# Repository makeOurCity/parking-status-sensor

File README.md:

# 満空灯カラーセンサ読み取り PoC 設計書

> 駐車場の満空表示灯（満／空灯）の発光色をカラーセンサで外付け読み取りし、満車・空車状態をIoTデータとして取得する実証（PoC）の設計書。

- ステータス: PoC 実証フェーズ（LTE-M 版の試作機で試験中、LoRaWAN 版を実装中）
- 最終更新: 2026-09-29
- 管理: GitHub（本設計書・Issues・実装コードを同一リポジトリで管理）

---

## 1. 背景と目的

### 1.1 背景

駐車場の満空状態を取得する一般的な方法は、各車室へのセンサ設置や、入退場ゲートと連動した在車台数カウントである。これらは駐車場設備側ですでに処理されており、外部から新規に取得しようとすると設備への介入が必要になる。

一方、多くの駐車場では満空状態が「満／空」表示灯として可視化されている。本PoCは、この**既存の表示灯を外側から読み取る**ことで、設備に手を加えずに満空データを取得できないかを検証する。

### 1.2 目的（PoCのゴール）

- 満空表示灯の発光色を外付けカラーセンサで読み取り、「満／空」を判定できることを確認する。
- 設備（制御盤・配線）に一切介入しない、外付け・単機能・設置容易な構成で成立することを示す。
- 取得したデータを既存のデータ基盤（FIWARE Orion / NGSIv2）に連携できる見通しを得る。

### 1.3 PoCで「やらないこと」（スコープ外）

- 長期間の安定運用・耐久性の実証（PoC期間は数週間〜数ヶ月を想定。電池容量はそれ以上の余裕あり）。
- ソーラー等による自立電源での無人長期運用（将来オプションとして記載のみ）。
- 全表示方式への対応（後述のとおり「色切替型」に限定）。
- 製品化・量産設計・外部提供。

---

## 2. 対象の限定

### 2.1 満空表示灯の方式分類

調査の結果、世の中の満空表示灯は概ね以下の4タイプに分類される。

| タイプ | 説明 | 本PoCでの扱い |
|---|---|---|
| 色切替型 | 同一表示面で赤（満）↔緑（空）など色が変わる。LED式の主流。 | **対象（本命）** |
| フルドット型 | フルドットLEDで満/空/混/閉やアイコン・文字を表示。 | スコープ外（将来検討） |
| 回転式（メカ式） | 物理的に板が回転して満/空を切替。非発光。 | スコープ外（光で読めない） |
| 多階・複合表示型 | 立体駐車場で階別満空を1枚に集約表示。 | スコープ外（多点必要） |

### 2.2 本PoCの前提

- 対象は **色切替型（赤=満／緑=空 など、色で状態が変わるLED式）** に限定する。
- 表示方式を絞らないと実証設計が発散するため、まず最も普及している方式で成立性を確認する。
- 設置にあたり、表示灯設置者の貼り付け許可は得られている前提とする。

### 2.3 想定現場数

- PoC初期は **2〜3現場** を想定。
- 目的は「現場ごとの光条件下で赤緑判定が安定するか」のパターン収集。

---

## 3. 方式：センサ直貼り

### 3.1 採用方式

カメラで表示灯を撮影する方式ではなく、**表示灯の発光面にカラーセンサを直接貼り付け、その一点の色と明るさを読む**方式を採用する。

### 3.2 カメラ方式を採らない理由

| 課題 | カメラ方式 | センサ直貼り方式 |
|---|---|---|
| 設置位置 | 表示灯前方に設置場所と画角確保が必要 | 発光面に密着、位置問題なし |
| 外光・昼夜 | 露出・白飛び・反射の影響を受ける | 黒カッティングシート積層で外光を物理的に遮断 |
| 遮蔽 | 車両の通過で視界が遮られる | 密着のため遮蔽の影響なし |
| 処理負荷・電力 | 画像処理が必要で消費電力大 | 色の閾値比較のみ、超低消費 |

### 3.3 貼り付けの構造

センサ部は数mm角のチップだが、現場設置では **Grove - I2C Color Sensor V3.0** を含む小型パッチユニットを、**透明テープと黒カッティングシートの積層**で発光面に固定する。

**対象満空灯の構造（PoC 初回現場）**

- 表示面 **385×391 mm**、**透明アクリルカバー**、**額縁で縁を覆う**構造。
- 縁へのクリップ固定は不可。吸盤は落下リスクがあり採用しない。
- **透明テープで面全体を固定**し、落下リスクをゼロにする（安全上最重要）。
- **黒カッティングシート**が遮光層を兼ね、外光の混入を抑える。

```
      表示灯の発光面（透明アクリル）
  ┌─────────────────────────────┐
  │   満／空 の光                │
  └──────────────┬──────────────┘
                 │ 光
  ┌──────────────▼──────────────┐  ← 透明テープで全面固定
  │ 黒カッティングシート（遮光）  │
  │   ┌─────────────┐           │
  │   │ Grove Color │ ← 受光部  │
  │   │ Sensor V3.0 │           │
  │   └──────┬──────┘           │
  └──────────┼──────────────────┘
             │ Grove 4芯ケーブル
       ESP32本体（別筐体）へ
```

**受光位置**

- 画像分析の結果、LED 配列上では **下から2行目・左から2列目** 付近が推奨。
- 黒シートにセンサ受光窓を切り抜き、Grove Color Sensor V3.0 の受光部を窓に合わせる。

**運用上の留意**

- 発光面に乗るのはパッチのみ。ESP32 本体・電源は Grove ケーブルで分離し、表示灯裏や柱に固定する。
- 脱着はテープを剥がすだけ。仮設 PoC 用途に適合する。
- パッチは数 cm 角程度で、385 mm 面に対して面積比は小さく視認性への影響は限定的。

### 3.4 色切替型での判定ロジック

- カラーセンサが返す R・G・B 値を比較し、`R - G ≥ threshold なら満（赤）`、`G - R ≥ threshold なら空（緑）` と判定。
- R と G の差が一定閾値未満の場合は「不明」とし、消灯・遷移中の誤判定を回避する。
- 現場ごとの閾値はサーバ側パラメータとして保持し、端末/サーバ双方で判定可能にする。

---

## 4. システム構成

### 4.1 信号の流れ

```
[満空灯の発光面] 赤=満 / 緑=空
      │ 光
      ▼
[センサパッチ]  Grove Color Sensor V3.0 + 黒シート積層固定
      │ Grove I2C ケーブル
      ▼
[XIAO ESP32S3 + Grove Shield]  赤か緑か判定・送信   ← 電源: LiPo 電池（§6）
      │ LTE-M / Wi-Fi: MQTT over TLS      LoRaWAN: AWS IoT Core for LoRaWAN（#40）
      ▼
[AWS IoT Core]  受け口（ルールでトリガー）
      │
      ▼
[AWS Lambda]  ブリッジ（ペイロード変換 → NGSIv2 upsert）  ※現在はスタブ（受信ログを CloudWatch Logs に記録するだけ）。本実装は #7
      │
      ▼
[FIWARE Orion]  満空を登録
      │
      ▼
[STH-Comet]  履歴蓄積・読み取り精度の検証
```

端末は Orion に直接書き込まない。MQTT ペイロードの変換と NGSIv2 への upsert は Lambda（ブリッジ）が担う。

### 4.2 判定の持たせ方（端末／サーバ両対応）

- 端末は「生のセンサ値（RGB＋輝度）」と「端末内の暫定判定結果」の両方を送信する。
- サーバ側は生値で再判定も、端末判定の採用も選べる。
- 現場別閾値テーブルをサーバに持ち、必要なら端末にも配信。判定ロジックを端末/サーバどちらに寄せるかを後から変更可能にする。

### 4.3 通信方式

通信モジュールごとに版を分ける。**ビルド環境（PlatformIO env）で版を選び、モジュールの自動判別や共存はしない**（Grove UART ポートを LTE-M と LoRaWAN で排他利用するため）。

| 版 | モジュール | 状況 | 使い分け |
|---|---|---|---|
| **LoRaWAN 版** | Grove Wio-E5（STM32WLE5JC、技適付き） | 実装中（#40） | **本流**。現場にゲートウェイを置ける場合。送信が短く電池に有利 |
| **LTE-M 版** | M5Stack SIM7080G CAT-M Unit（M5STACK-U128）+ SORACOM SIM（plan-D / plan-KM1） | 実装済み・現地試験済み | LoRaWAN でどうしても通信できない場合 |
| Wi-Fi | ESP32-S3 内蔵 | ファーム対応済み | Wi-Fi を使える環境 |

- LTE-M 版は、送信するときだけ**ロードスイッチ基板**で LTE-M の電源を入れる（#88、基板評価中）。モデム内蔵の TLS で AWS IoT Core に直接つなぐ。旧方式のラッチングリレー（#46）は廃止した（経緯: [docs/25-low-power-phase2-hardware-cutoff.md](docs/25-low-power-phase2-hardware-cutoff.md) §2）。
- 送信データは判定結果＋生値のみで極小（数百バイト程度）。LoRaWAN の典型的なペイロードにも収まる。
- ファームの env と設定は [firmware/README.md](firmware/README.md) を参照。

### 4.4 FIWARE連携

- 満空フラグをNGSIv2でOrionにupsert。
- PoC段階では標準データモデルにこだわらず、独自エンティティ（例: `ParkingStatusSensor`）に `status`（満/空/不明）・生センサ値・タイムスタンプを載せる。
- STH-Cometで履歴化し読み取り精度を検証。方式確定後に `OffStreetParking` 等の標準属性へマッピングし直す。
- 投入は既存の moc-skill / GeonicDB CLI で運用可能。

---

## 5. 部品リスト（BOM）

### 5.1 確定BOM（試作1台分）

| 部品 | 型番 | 入手先 | 価格 | 備考 |
|---|---|---|---|---|
| マイコン | Seeed XIAO ESP32S3（無印） | 秋月電子 | ¥1,480 | 技適取得済(217-230892)。BAT はパッドのみ（JST 非搭載） |
| Grove Shield | Grove Shield for XIAO（103020312） | Seeed JP 等 | 約¥700 | 8×Grove（I2C×2・UART×1）。BAT パッド・充電管理付き |
| カラーセンサ | Grove - I2C Color Sensor V3.0（101021133） | Seeed Studio 等 | 約¥600 | VEML6040 搭載。I2C `0x10`。Grove コネクタ内蔵 |
| センサ接続 | Grove 4芯ケーブル 50〜100cm | Seeed / Amazon 等 | 約¥200〜400 | 標準配線（ピン入替不要。[wiring.md](docs/wiring.md)） |
| 閾値調整用ポテンショメーター | Grove - Rotary Angle Sensor | Seeed 等 | — | 現地での判定閾値の調整用（#60）。調整後は外してよい |
| バッテリー | LiPo 3.7V 4,400mAh 保護回路内蔵 JST-PH | ストロベリーリナックス | ¥550 | Grove Shield の BAT パッドへ JST で接続 |
| 配線・防水箱・固定材 | Grove ケーブル、IP65 樹脂箱、透明テープ・黒カッティングシート等 | Seeed / ホームセンター | 約¥2,000〜3,000 | 詳細は [docs/hardware.md](docs/hardware.md) 参照 |

**通信モジュール（版ごとにどちらか）**

| 部品 | 型番 | 入手先 | 価格 | 備考 |
|---|---|---|---|---|
| LoRaWAN モジュール | Grove - Wio-E5 | Seeed 等 | — | LoRaWAN 版。Grove UART 接続。常時通電 |
| LTE-M モジュール | M5Stack SIM7080G CAT-M Unit（M5STACK-U128） | スイッチサイエンス | ¥6,908 | LTE-M 版。Grove UART 接続 |
| SIM | SORACOM IoT SIM plan-D / plan-KM1 | SORACOMストア | ¥990（初期）+ ¥192/月〜 | LTE-M 版。ドコモ / KDDI 回線 |
| LTE-M 電源スイッチ基板 | 自作小基板 rev A（TI TPS22918、[hardware/lte-power-switch/](hardware/lte-power-switch/)） | JLCPCB（基板 + 実装） | $20.14（5 枚、送料込み） | LTE-M 版。LTE-M の電源を送信時だけ入れる（#88）。**rev A は Grove コネクタのピン番号が鏡像で、普通のケーブルでは使えない。rev B（2026-10-12 発注、$30.61）で直した** |

- 詳細な選定経緯・調達先 URL は [docs/hardware.md](docs/hardware.md)・[docs/bom.md](docs/bom.md) を参照。

### 5.2 部品選定の要点

- **マイコン**: カメラ不要なため無印 XIAO ESP32S3 で十分（Sense 版は不要）。LiPo 充電管理は Grove Shield 側にある。
- **センサ**: **Grove - I2C Color Sensor V3.0**（VEML6040 搭載）。
- **接続方式**: センサ・通信モジュール・LTE-M 電源スイッチ基板はすべて **Grove で接続**する（ピン入替・はんだ付け不要）。汎用性と組み立ての容易さを両立させ、LoRaWAN 版と LTE-M 版で構成を揃える。
- **バッテリー**: LiPo 電池を **Grove Shield の BAT パッド**に JST で接続（XIAO 本体には JST コネクタ非搭載）。モバイルバッテリーはオートパワーオフおよびパススルー時の瞬断が問題になるため不採用。

---

## 6. 電源方針

### 6.1 電源構成

- **LiPo 電池（3.7V 4,400mAh、保護回路内蔵）**を Grove Shield for XIAO の **BAT パッド**に JST で接続して運用する（はんだ付け前にテスターで極性を確認）。電源を引ける現場では USB 給電でも可。
- 電池で動かしているとき、**ESP32-S3 と Grove の各ポート（センサー・LTE-M を含む）は、Shield 上の降圧コンバーター（ETA3410）の 3.3V を共有する**。5V 系統は無効で、昇圧回路は使わない（[docs/hardware.md](docs/hardware.md)）。
- LTE-M モジュールは、送信するときだけロードスイッチ基板で通電する（#88、基板評価中）。
- 起床間隔は 5 分（`PSS_SLEEP_SECONDS=300`）。LTE-M 版は**状態が変わったときだけ送信**し、変わらなければ約 66 分に 1 回だけ定期送信する（`PSS_CHANGE_ONLY_SEND=1`、`PSS_HEARTBEAT_CYCLES=12`）。満空情報に秒単位の即時性は不要なので、この遅延は許容できる。

### 6.2 消費電力と稼働日数（LTE-M 版）

実測値（2026-09-29、`xiao-s3-aws-lte-relay-pot`、U200-1A 高速ロガーで約 44.5h 記録。詳細: [docs/74-brownout-conclusions.md](docs/74-brownout-conclusions.md) §4）:

| 項目 | 実測値 |
|---|---|
| Deep Sleep 中の電流 | 0.43 mA |
| 送信する起床 1 回（起床〜LTE 接続〜MQTT 送信〜切断〜Deep Sleep） | 16.8 秒・0.446 mAh |
| 送信しない起床 1 回（センサー読み取りのみ） | 4.8 秒・0.0475 mAh |

稼働日数の目安（LiPo 実効 3,960 mAh = 4,400 mAh × 90%）:

| シナリオ | 稼働日数 |
|---|---|
| 状態変化なし（約 66 分に 1 回の定期送信のみ） | **約 122 日** |
| 状態変化 1 日 20 回 | 約 98 日 |
| 毎回送信（worst case） | 約 29 日 |

**電池残量と充電の目安:** LTE-M 版は、電池の電圧が下がると LTE の送信時にブラウンアウトリセットが起き始める。1 回だけなら実害はほぼないが、そのまま放置すると送信できなくなる。**1 回目のブラウンアウト（テレメトリの `resetReason=brownout`）を「すぐ充電」の合図として扱う**。実際に使える日数は、上の表より短くなる（[docs/74-brownout-conclusions.md](docs/74-brownout-conclusions.md) §3.1）。

**LoRaWAN 版:** 送信が短く、TLS も不要なので、LTE-M 版より消費は小さい見込み（未実測、#40）。ゲートウェイを置ける現場では LoRaWAN を優先する（§4.3）。

### 6.3 ソーラー併用（将来オプション・PoCでは不採用）

将来の長期自立運用フェーズでのオプションとして記載のみ。初期PoCでは以下の理由で**不採用**とする。

- ソーラーパネルが現時点で比較的高価。
- 駐車場の設置状況により十分な日照が得られるか不明で、現地確認が前提。
- PoC段階では長期安定運用が要件外。

採用する場合の候補・留意点:
- 候補: MOTTERU MOT-SOLAR24（最大24W, USB-A, IP65）、Anker Solix PS30（27W, IP65）等。
- IP65防水はパネル部のみの製品が多く、パネルのみ屋外・バッテリ/ESP32は防水箱に収納。
- ソーラー併用時はバッテリーの「パススルー充電対応」「充放電切替時の出力瞬断なし」「低負荷時も高効率な充電制御IC(MPPT等)」を満たす機種を現物確認。

---

## 7. 関連事例・新規性

### 7.1 同種事例の調査結果

| 区分 | 状況 |
|---|---|
| 満空灯を後付け読み取りする事業・製品 | 見当たらない（応用先として空いている） |
| ほぼ同じ個人試作 | 1件あり。機器の電源ランプの色をカラーセンサ(S11059)＋ESP32で読む試作。「消灯=黒」の判定に課題。本設計の「差が小さければ不明」処理の妥当性を裏付け |
| 上位概念（表示灯の後付けIoT化） | 確立済み。PATLITE WDシステム（信号灯の後付けIoT化）等の製品、複数の特許が存在。技術的成立性は実証済み |

### 7.2 新規性の位置づけ

- 「光センサで人間用表示灯を外側から読みIoT化する」技術自体は枯れており、成立性は担保されている。
- 「**駐車場満空灯 × 自治体オープンデータ／FIWARE連携**」という応用は明確な先行事例が見当たらず、応用先として空いている。
- PoCで確かめるべきは技術成立性ではなく「現場光条件での赤緑安定判定」に集約される。

---

## 8. リスクと検証項目

### 8.1 PoCで潰す検証項目（優先順）

1. **生値の分離**: Grove Color Sensor V3.0（VEML6040）の R/G/B/W 生値が、満（赤）と空（緑）で十分なマージンを持って分離するか。透明カバー越し・拡散材ありの実機で確認。
2. **2状態以外の表示**: 消灯・点滅・整備中・深夜消灯等が現場にあるか棚卸しし、判定テーブルに「不明」状態を持たせる。
3. **電源運用**: 電池の電圧が下がったときにブラウンアウトが起き始める残量の確認（LTE-M 版、[docs/74-brownout-conclusions.md](docs/74-brownout-conclusions.md) §2.4）。LoRaWAN 版の消費電力の実測（#40）。

### 8.2 特許リスク

調査した米国特許 US11962293B2「Passive optical sensors」の権利範囲を確認した結果:

- この特許の新規部分は「**受動回路（FET＋蓄電）で、リレー接点ON/OFFのようなバイナリ出力を無電源で作る**」という回路構成にある。「ランプを光で読む」という目的自体は権利化されていない。
- 本PoC方式は「**能動的なマイコン(ESP32)＋デジタルI2Cカラーセンサ＋ソフトウェア判定**」であり、構成・動作原理が別物。抵触する見込みは低い。
- むしろ本方式は、当該特許が「従来技術（課題あり）」と位置づけるデジタルセンサ側であり、特許の新規部分の外側にある。
- ESP32＋カラーセンサでランプ色を読む構成は公知（個人事例あり）。

リスク評価:
- **PoC段階（社内技術検証）**: 試験・研究目的の実施に当たり、特許侵害の問題はほぼ生じない（一般論。最終判断は弁理士領域）。
- **事業化段階**: 以下を実施。
  1. 受動光センサ特許の他、PATLITE WDシステム関連等の関連特許を調査。
  2. 国内特許（対応日本出願・別の国内特許）の有無を確認。
  3. 弁理士によるFTO（Freedom to Operate）確認。

---

## 9. データモデル

取得したセンサデータは NGSIv2 エンティティ `ParkingStatusSensor` として FIWARE Orion に登録する。センサ1台 = エンティティ1件の 1:1 構成で、駐車場の集約や台数管理は行わない。端末の MQTT ペイロード（`raw`・`timestamp` 等）と NGSIv2 属性名（`rawSensor`・`dateObserved` 等）は異なるため、AWS Lambda（ブリッジ）で変換する。将来的に `OffStreetParking`（FIWARE Smart Data Models）へマッピングする想定だが、PoC段階では `ParkingStatusSensor` 単体で完結させる。

詳細は [docs/data-model.md](docs/data-model.md) を参照。

---

## 10. 次のステップ

タスクは GitHub Issues で管理しています。**全体ロードマップは [Issue #22](https://github.com/makeOurCity/parking-status-sensor/issues/22)** を参照。

| Milestone | 状況 | 残っている主な Issue |
|---|---|---|
| [M1: 試作1台 通電](https://github.com/makeOurCity/parking-status-sensor/milestone/1) | 完了 | — |
| [M2: クラウド E2E](https://github.com/makeOurCity/parking-status-sensor/milestone/2) | 端末 → AWS IoT Core → Lambda（スタブ）まで完了 | #7 Lambda の本実装（NGSIv2）、#27 組織クラウド環境 |
| [M3: 現場 PoC](https://github.com/makeOurCity/parking-status-sensor/milestone/3) | 進行中 | #8 生値分離テスト、#2 棚卸し |

マイルストーン外の主な進行中の作業: #40 LoRaWAN 版、#12 筐体。

---

## 付録: リポジトリ構成

```
parking-status-sensor/
├── README.md                  # 本設計書
├── AGENTS.md                  # 開発運用（GitHub Flow・ドキュメント運用）
├── docs/
│   ├── hardware.md            # 部品選定・給電経路・稼働日数試算
│   ├── bom.md                 # 詳細BOM（試作1台）
│   ├── schematic.md           # 回路図
│   ├── wiring.md              # 組み立て手順・実物確認
│   ├── data-model.md          # NGSIv2 エンティティ設計
│   ├── iot-core.md            # AWS IoT Core 設計（#4）
│   ├── aws-admin-handoff.md   # AWS 管理者向けセットアップ手順
│   ├── sync-delivery-design.md # 送信確認・再送（sync ledger）の設計
│   ├── power-measurement.md   # 消費電力の計測手順
│   ├── NN-*.md                # Issue ごとの設計・調査（例: 74-brownout-conclusions.md）
│   └── datasheets/            # 回路図・データシート
├── firmware/                  # ESP32 ファームウェア（PlatformIO、版ごとの env）
├── hardware/
│   └── flame-sensor-case/     # Grove センサ用ケースの 3D モデル（第三者作品・CC BY 4.0、#3）
├── bridge/                    # Lambda ブリッジ（現在はスタブ → #7 で本実装）
├── infra/                     # AWS IoT Core・Cognito のプロビジョニングスクリプト
└── tools/
    ├── power-logger/          # U200-1A 電源ロガー（通常・高速モード）
    ├── log-viewer/            # CloudWatch Logs 閲覧用 iOS アプリ
    ├── soracom/               # SORACOM SIM の状態確認
    ├── mosquitto/             # ローカル MQTT ブローカー（開発用）
    └── ipad-sign-simulator/   # 満空表示灯を iPad 画面で模擬する検証用アプリ（#54）
```

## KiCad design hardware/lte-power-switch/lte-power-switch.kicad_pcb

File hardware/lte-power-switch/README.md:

# LTE power switch（Issue #88）

**状態: 暫定・WIP。rev A（2026-10-05 発注、2026-10-12 到着）は、Grove コネクタのピン番号が実物と鏡像のため、普通の Grove ケーブルでは使えない（下の「rev A の既知の不具合」）。このディレクトリの設計・製造データは、鏡像を直した rev B（2026-10-12 作成・発注）。** M5 Unit CatM（LTE-M）の VCC 線を TI TPS22918DBVR で開閉する、Grove コネクタ 3 つの小基板。設計の背景は [../../docs/88-load-switch-design.md](../../docs/88-load-switch-design.md)。

| コネクタ | 向き | 内容 |
|---|---|---|
| J1 IN | 左辺 | Shield の UART Grove ポートから。pin1/pin2 は J2 へ直結、pin3 = 3V3（`V3V3_IN`）、pin4 = GND |
| J2 OUT | 右辺 | LTE-M ユニットへ。pin1/pin2 は J1 から直結、pin3 = スイッチ後（`VLTE`）、pin4 = GND |
| J3 CTRL | 下辺 | Shield の D0（GPIO1）から。pin1 = `LTE_EN`（HIGH で ON）、pin4 = GND、**pin2/pin3 は未接続**（5V ポートに誤挿入しても被害が出ないように） |

Grove の pin1 = 黄、pin2 = 白、pin3 = 赤、pin4 = 黒。**物理的なパッドの並びは、三角（J1 は▼、J2 は▲、J3 は▶）のパッドから順に、pin4（黒・GND）、pin3（赤）、pin2（白）、pin1（黄）**（下の「rev B」の表）。基板は 38 × 28mm、2 層、1.6mm。部品はすべて表面（JLCPCB の片面実装）。

## 部品（JLCPCB、2026-10-05 に jlcpcb.com の部品検索で在庫と区分を確認）

| 参照 | 部品 | LCSC | 区分 | 在庫 |
|---|---|---|---|---|
| U1 | TPS22918DBVR（SOT-23-6） | C131941 | Extended | 12,774 |
| J1〜J3 | CAX HY2.0-4P-WT（SMD 直角） | C722729 | Extended | 2,954 |
| C1 | 1µF 50V X5R 0603 | C15849 | Basic | 7,179,042 |
| C2 | 1nF 50V X7R 0603（差し替え可、例: 2.2nF） | C1588 | Basic | 7,779,974 |
| R1 | 100kΩ 1% 0603（ON ピンのプルダウン、必須） | C25803 | Basic | 22,053,367 |
| R2 | 0603、**DNP**（QOD と VOUT の間。実装すると QOD 有効） | — | — | — |
| C3 | 10µF 10V X5R 0603、**DNP**（任意。C19702 が Basic） | C19702 | Basic | 10,364,993 |
| TP1〜TP4 | 1.5mm 円形パッド（V3V3_IN / VLTE / LTE_EN / GND）。実装しない | — | — | — |

## ファイル

- `lte-power-switch.kicad_pro` / `.kicad_sch` / `.kicad_pcb`: KiCad 10.0.6 のプロジェクト。`lte-power-switch.kicad_sym` と `lte-power-switch.pretty/` は TPS22918 の記号とフットプリント（LCSC/EasyEDA 由来のパッド寸法。`3dmodels/` も同じ出典）。
- `lte-power-switch-schematic.pdf`: 回路図。
- `renders/`: 表・裏の SVG と 3D 画像。
- `fabrication/`: `lte-power-switch-gerber.zip`（ガーバー + ドリル。注文用）、`lte-power-switch-bom.csv`、`lte-power-switch-cpl.csv`、`erc.rpt`、`drc.rpt`、`gerber/`（展開済み）。**rev B のデータ。** rev A の注文データは、git の履歴（PR #117 のマージ時点、`eb54a1a`）にある。
- `scripts/`: 回路図・基板・製造データの生成スクリプト（`gen_lib.py` → `gen_sch.py` → `run_pcb.sh` → `make_fab.py` の順）。製造データの確認用に、`check_gerber_connectivity.py`（ガーバーとドリルから銅箔の接続を求め、ネットの断線・ショート、J1〜J3 のパッド順を検査する。`python3 scripts/check_gerber_connectivity.py`）がある。回路図と基板は手書きではなくスクリプトから生成している。KiCad で編集した場合、スクリプトを再実行すると上書きされる。

## rev A の既知の不具合（2026-10-12、実機で確認）

**J1・J2・J3 のコネクタ（HY2.0-4P-WT）の pad 番号が、実物と鏡像になっている。** Grove ケーブルを挿すと、▼（J2 は▲、J3 は▶）のマークに一番近いパッド（設計の pin1）に**黒（GND）**が来る。設計では、そこは pin1 = 黄（SIG1）。

| 位置（三角に近い順） | 設計（回路図・基板） | 実際にそこへ来る Grove ケーブルの線 |
|---|---|---|
| 1 番目（三角のパッド） | pin1 = SIG1（黄） | 黒（GND） |
| 2 番目 | pin2 = SIG2（白） | 赤（VCC） |
| 3 番目 | pin3 = 3V3 / VLTE（赤） | 白 |
| 4 番目 | pin4 = GND（黒） | 黄 |

- 回路図（論理）は正しい。誤りは、フットプリントの pad 番号（pad「1」を、実物の pin1 と逆の端に置いた）。
- 原因: 下の「発注前に確認すること」2 を、実物で確認しないまま発注した。
- 影響: 普通の Grove ケーブルを J1・J2 につなぐと、Shield の VCC と GND が信号線のパッドにつながる。**rev A を、普通のケーブルで Shield に挿さないこと。**
- rev A の使い方（検証のみ）: ケーブルの片側を切って、テストポイント（`3V3` / `GND` / `EN` / `VLTE`）に直結する。
- 直し方（rev B）: フットプリントの pad 番号を逆にする（1↔4、2↔3）。回路図は変えない。基板のコネクタまわりの配線は、引き直しになる。

**rev A の動作確認（テストポイント直結、2026-10-12）:** Shield の 3.3V を `3V3` TP に入れ、`EN` を `3V3` につなぐと、`VLTE` が 3.3V になった。外すと、1 秒以内に 0V に戻った（負荷なし、QOD 開放）。U1 の向きは正しい。

**LTE-M・実機ファームでの確認（2026-10-12）:** 逆結線の専用ケーブルで、Shield・U128 につなぎ、ブートモードの送信 2/5〜5/5（LTE-M の接続、MQTT）が、途中でリセットされずに完了した。OFF のときの `VLTE` は、UART が動いている間は約 0.76V（旧リレー方式と同程度）、Deep Sleep では、20〜30 秒で 0V になった。回路の変更は、要らない見込み。

**1 号機の実機での消費電力の実測（2026-10-13）:** Deep Sleep の待機電流は **平均 0.40 mA**（旧リレー方式は 0.45 mA）、送信 1 回は **0.42 mAh**（LTE の接続 7.5 秒）〜 1.14 mAh（接続 30.5 秒）。起床のたびに、スイッチは ON → OFF し、ブートモードの 5 回、状態変化の送信、定期送信（約 66 分ごと）が、すべて届いた。電圧降下（0.6A）と、突入電流の詳しい波形は、未確認（[docs/88-load-switch-design.md](../../docs/88-load-switch-design.md) §8）。

## rev B（2026-10-12 作成・発注）

rev A の鏡像の不具合を直した版。**回路図（論理）は rev A と同じ**で、変えたのは、フットプリントと配線と印字。

**変更点**
- コネクタ（HY2.0-4P-WT）のフットプリントの pad 番号を逆にした（1↔4、2↔3。rev A の実測で、実物の pin1 = 黄線は、+X 側）。
- コネクタまわりの配線を引き直した（V3V3_IN、VLTE、LTE_EN、SIG1、SIG2、GND のビア）。SIG1・SIG2 は、裏面の入れ子の U 字（交差なし）。TP2 は、VLTE の線の上に移した。U1・C1・C2・R1・R2・C3 と、J1〜J3 の位置・向きは、rev A と同じ（JLCPCB の CPL も同じ）。
- 三角（▼・▲・▶）の位置は、物理的に同じ。そこは GND（黒）のパッドになった。各コネクタの横に、「tri=GND(black)」と注記し、裏面に、全ピンの対応表を印字した。
- テストポイント（丸いパッド）は、rev A のまま。

**確認したこと（2026-10-12）**
- KiCad の DRC: 違反 0 件、未配線 0 件、回路図との不整合 0 件。ERC: 違反 0 件。
- `scripts/check_gerber_connectivity.py`: 製造用ガーバーから銅箔の接続を求め、10 ネットすべてが 1 つの塊で、ショートなし。J1〜J3 の物理的なパッド順が、実物の Grove ケーブルの順（三角から 黒・赤・白・黄）と一致する。**rev A のデータでは、同じチェックが、J1〜J3 で失敗する**（鏡像を検出できる）。
- 未確認: 実際に製造した基板での確認（rev A と同じ手順）。

**発注（2026-10-12）:** JLCPCB、PCB/PCBA、各 5 枚。注文番号 W2026101217460284、2026-10-12 18:46。商品 $20.90 + 送料 $9.71 = **$30.61**（rev A は $20.14。新規ユーザーのクーポンが効いていた額で、今回は効いていない）。内訳は、PCB（注文番号 Y3-13728224A）$2.00、実装 $20.48（注文画面の表示）。BOM・CPL・ガーバーは、`fabrication/` のデータ（BOM・CPL は rev A と同一）。

**注文画面（PCBA Viewer）での確認（2026-10-12）:** U1 の pin1（紫のマーク）は、左上のパッドで、rev A と同じ向き。

**物理的なパッド順（▼・▲・▶のパッドから順）と、印字**

| 位置 | J1（IN、Shield の UART へ） | J2（OUT、LTE-M へ） | J3（CTRL、Shield の D0 へ） |
|---|---|---|---|
| 1（三角のパッド） | GND（黒） | GND（黒） | GND（黒） |
| 2 | 3V3（赤） | VLTE（赤） | NC（赤。3V3 は未接続） |
| 3 | TX-6（白） | RX（白。モジュールの RX） | NC（白。D1 は未接続） |
| 4 | RX-7（黄） | TX（黄。モジュールの TX） | LTE_EN / D0（黄） |

- 三角は、**GND 側の端**（Shield の Grove ポートは、GND が端、その隣が 3V3）。
- J1 と J2 の信号線は、ケーブルがまっすぐなので、同じ位置にある。J1 は XIAO から見た名前（TX-6・RX-7）、J2 はモジュールから見た名前。
- **J3 の白（D1）は、NC のままにする。** Shield の右上ポート（D0・D1）の白線は、右下ポート（ポテンショメーター、D1・D2）の黄線と、同じ D1 の線。つなぐと、ポテンショメーターの信号に干渉する。赤（3V3）も、誤挿入しても何も入らないよう、未接続のまま。

**Shield（Grove Shield for XIAO）のポートの印字（2026-10-12、写真で確認。左から 1 番目〜4 番目 = 黄・白・赤・黒）**

| ポート | 黄 | 白 | 赤 | 黒 | 用途 |
|---|---|---|---|---|---|
| 左上（I2C） | SCL-5 | SDA-4 | 3V3 | GND | カラーセンサー |
| 左下（UART） | RX-7 | TX-6 | 3V3 | GND | J1 |
| 右上 | D0 | D1 | 3V3 | GND | J3 |
| 右下 | D1 | D2 | 3V3 | GND | ポテンショメーター |

- 左下の「RX」「TX」は、写真では頭文字が切れていて、ファームの定義（D7 = RX、D6 = TX）からの推定。

## 発注前に確認すること（rev A 発注時の項目。rev B の発注前にも、確認する）

1. **JLCPCB の注文画面（PCBA Viewer）で、U1 と J1〜J3 の向きを確認する。** rev A では、JLCPCB のエンジニアが、U1 の 1 点だけを修正した（修正の中身は不明。修正後の実装で、実機は正常に動作した）。rev B の CPL は、U1 と J1〜J3 の位置・向きが rev A と同じなので、同様に確認する。`fabrication/lte-power-switch-cpl.csv` の回転角は KiCad の値そのまま（補正なし）。フットプリントは LCSC/EasyEDA の公開ライブラリ由来なので補正が不要の可能性が高いが、自動では確認できていない。ずれていれば、注文画面で回転を直す。
2. **HY2.0-4P-WT が手元の Grove ケーブルと嵌合し、pin1 が黄線になるか。（rev A では、未確認のまま発注し、鏡像だった。rev B は、rev A の実物で確認した並びに合わせてあり、`check_gerber_connectivity.py` で検査できる。）** データシートに pin1 の位置の記載はなく、フットプリントの pin1（嵌合口を手前にして左端）は EasyEDA の定義による。最初の 1 枚で、ケーブルを J1 に挿し、反対側の黄線と基板の pin1 パッド（三角マーク側）の導通を確認する。
3. パッドの寸法は LCSC のライブラリ由来で、データシート（外形の図のみ）では検証できていない。

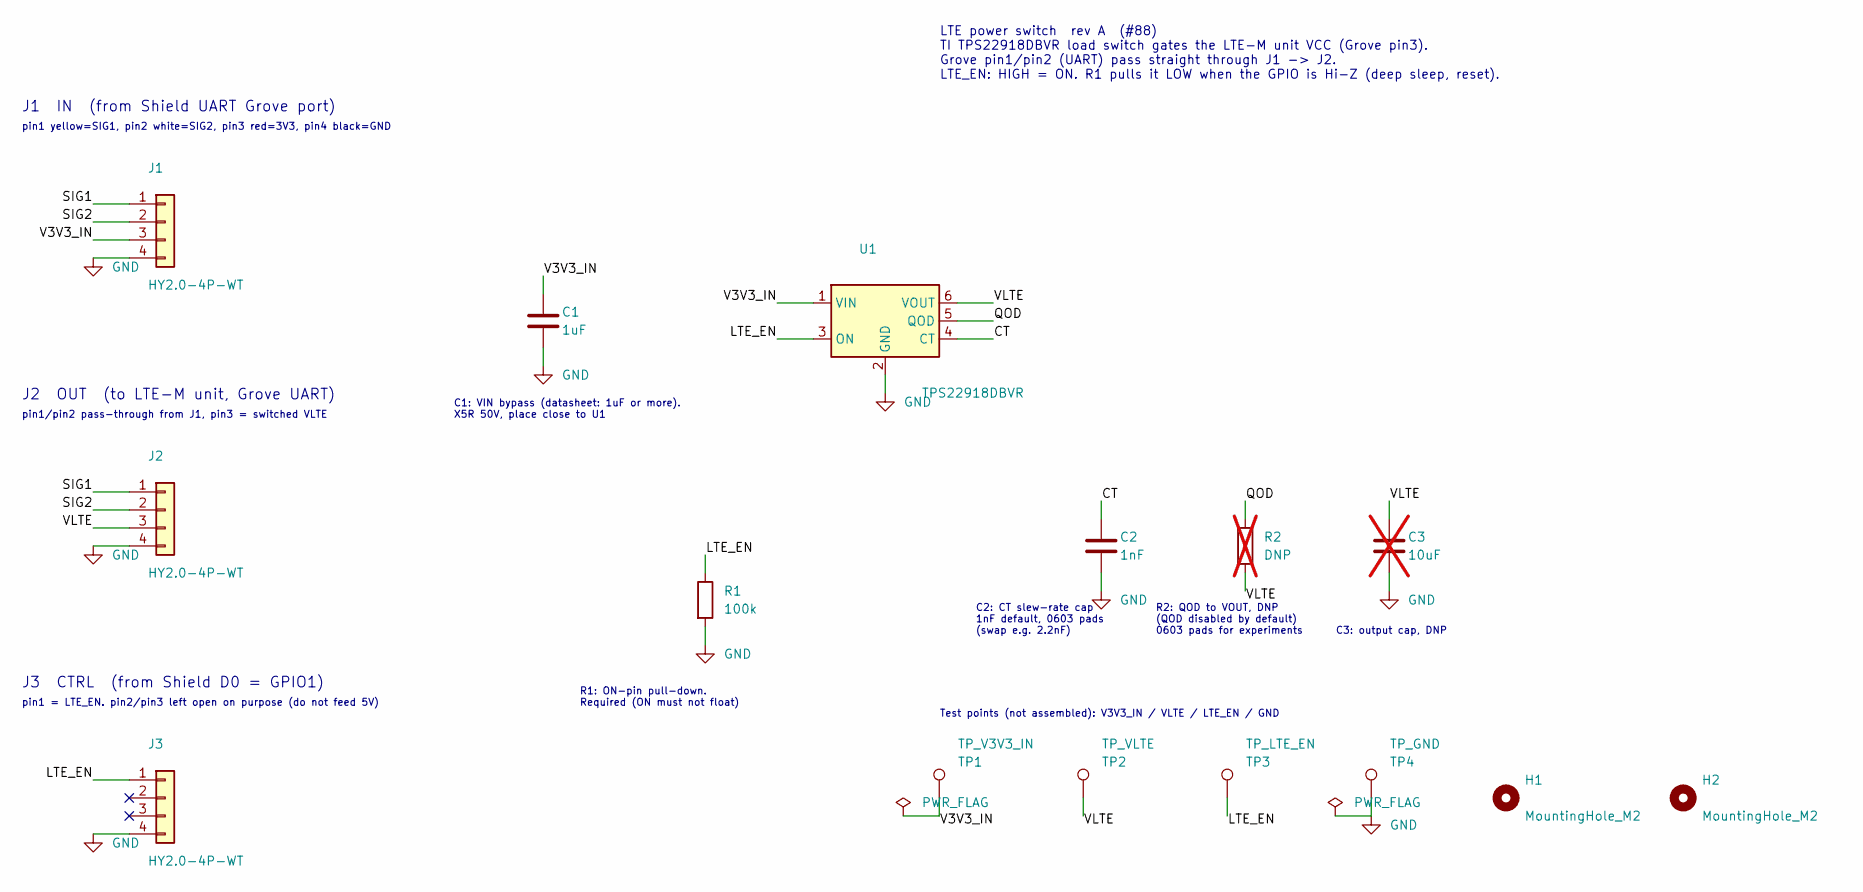
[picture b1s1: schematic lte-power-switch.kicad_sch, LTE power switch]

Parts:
C1: 1uF; C_0603_1608Metric; LCSC C15849
C2: 1nF; C_0603_1608Metric; LCSC C1588
C3: 10uF; C_0603_1608Metric; LCSC C19702; not fitted
H1, H2: MountingHole_M2; MountingHole_2.2mm_M2
J1, J2, J3: HY2.0-4P-WT; HY2.0-4P-WT_SMD-RA; LCSC C722729
R1: 100k; R_0603_1608Metric; LCSC C25803
R2: DNP; R_0603_1608Metric; not fitted
TP1: TP_V3V3_IN; TestPoint_Pad_D1.5mm
TP2: TP_VLTE; TestPoint_Pad_D1.5mm
TP3: TP_LTE_EN; TestPoint_Pad_D1.5mm
TP4: TP_GND; TestPoint_Pad_D1.5mm
U1: TPS22918DBVR; SOT-23-6_TPS22918DBVR; LCSC C131941

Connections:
/CT: C2.1, U1.4 (CT)
/LTE_EN: J3.1, R1.1, TP3.1, U1.3 (ON)
/QOD: R2.1, U1.5 (QOD)
/SIG1: J1.1, J2.1
/SIG2: J1.2, J2.2
/V3V3_IN: C1.1, J1.3, TP1.1, U1.1 (VIN)
/VLTE: C3.1, J2.3, R2.2, TP2.1, U1.6 (VOUT)
GND: C1.2, C2.2, C3.2, J1.4, J2.4, J3.4, R1.2, TP4.1, U1.2 (GND)

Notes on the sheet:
pin1 yellow=SIG1, pin2 white=SIG2, pin3 red=3V3, pin4 black=GND
J3 CTRL (from Shield D0 = GPIO1)
C1: VIN bypass (datasheet: 1uF or more). X5R 50V, place close to U1
J1 IN (from Shield UART Grove port)
C3: output cap, DNP
pin1 = LTE_EN. pin2/pin3 left open on purpose (do not feed 5V)
pin1/pin2 pass-through from J1, pin3 = switched VLTE
Test points (not assembled): V3V3_IN / VLTE / LTE_EN / GND
LTE power switch rev A (#88) TI TPS22918DBVR load switch gates the LTE-M unit VCC (Grove pin3). Grove pin1/pin2 (UART) pass straight through J1 -> J2. LTE_EN: HIGH = ON. R1 pulls it LOW when the GPIO is Hi-Z (deep sleep, reset).
C2: CT slew-rate cap 1nF default, 0603 pads (swap e.g. 2.2nF)
J2 OUT (to LTE-M unit, Grove UART)
R1: ON-pin pull-down. Required (ON must not float)
R2: QOD to VOUT, DNP (QOD disabled by default) 0603 pads for experiments

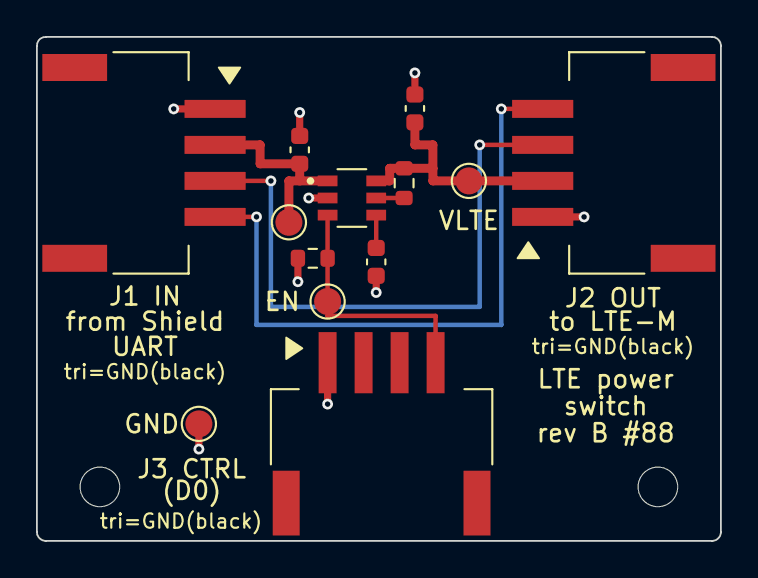
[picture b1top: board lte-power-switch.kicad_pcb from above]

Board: 2 copper layers, 38.0 x 28.0 mm, 15 parts (0 on the bottom side), 8 nets.
